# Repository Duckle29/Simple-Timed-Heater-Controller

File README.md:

# Simple-Timed-Heater-Controller
A simple controller used to manage electrical heaters in for example a shed.
This code is compatible with any arduino board. It has however only been tested on my own hardware.

### Libraries used
In order to use the firmware, you will need to have the following libaries in your library folder:

* [LiquidTWI2](https://github.com/lincomatic/LiquidTWI2)
* [Encoder by PJRC](https://www.pjrc.com/teensy/td_libs_Encoder.html)

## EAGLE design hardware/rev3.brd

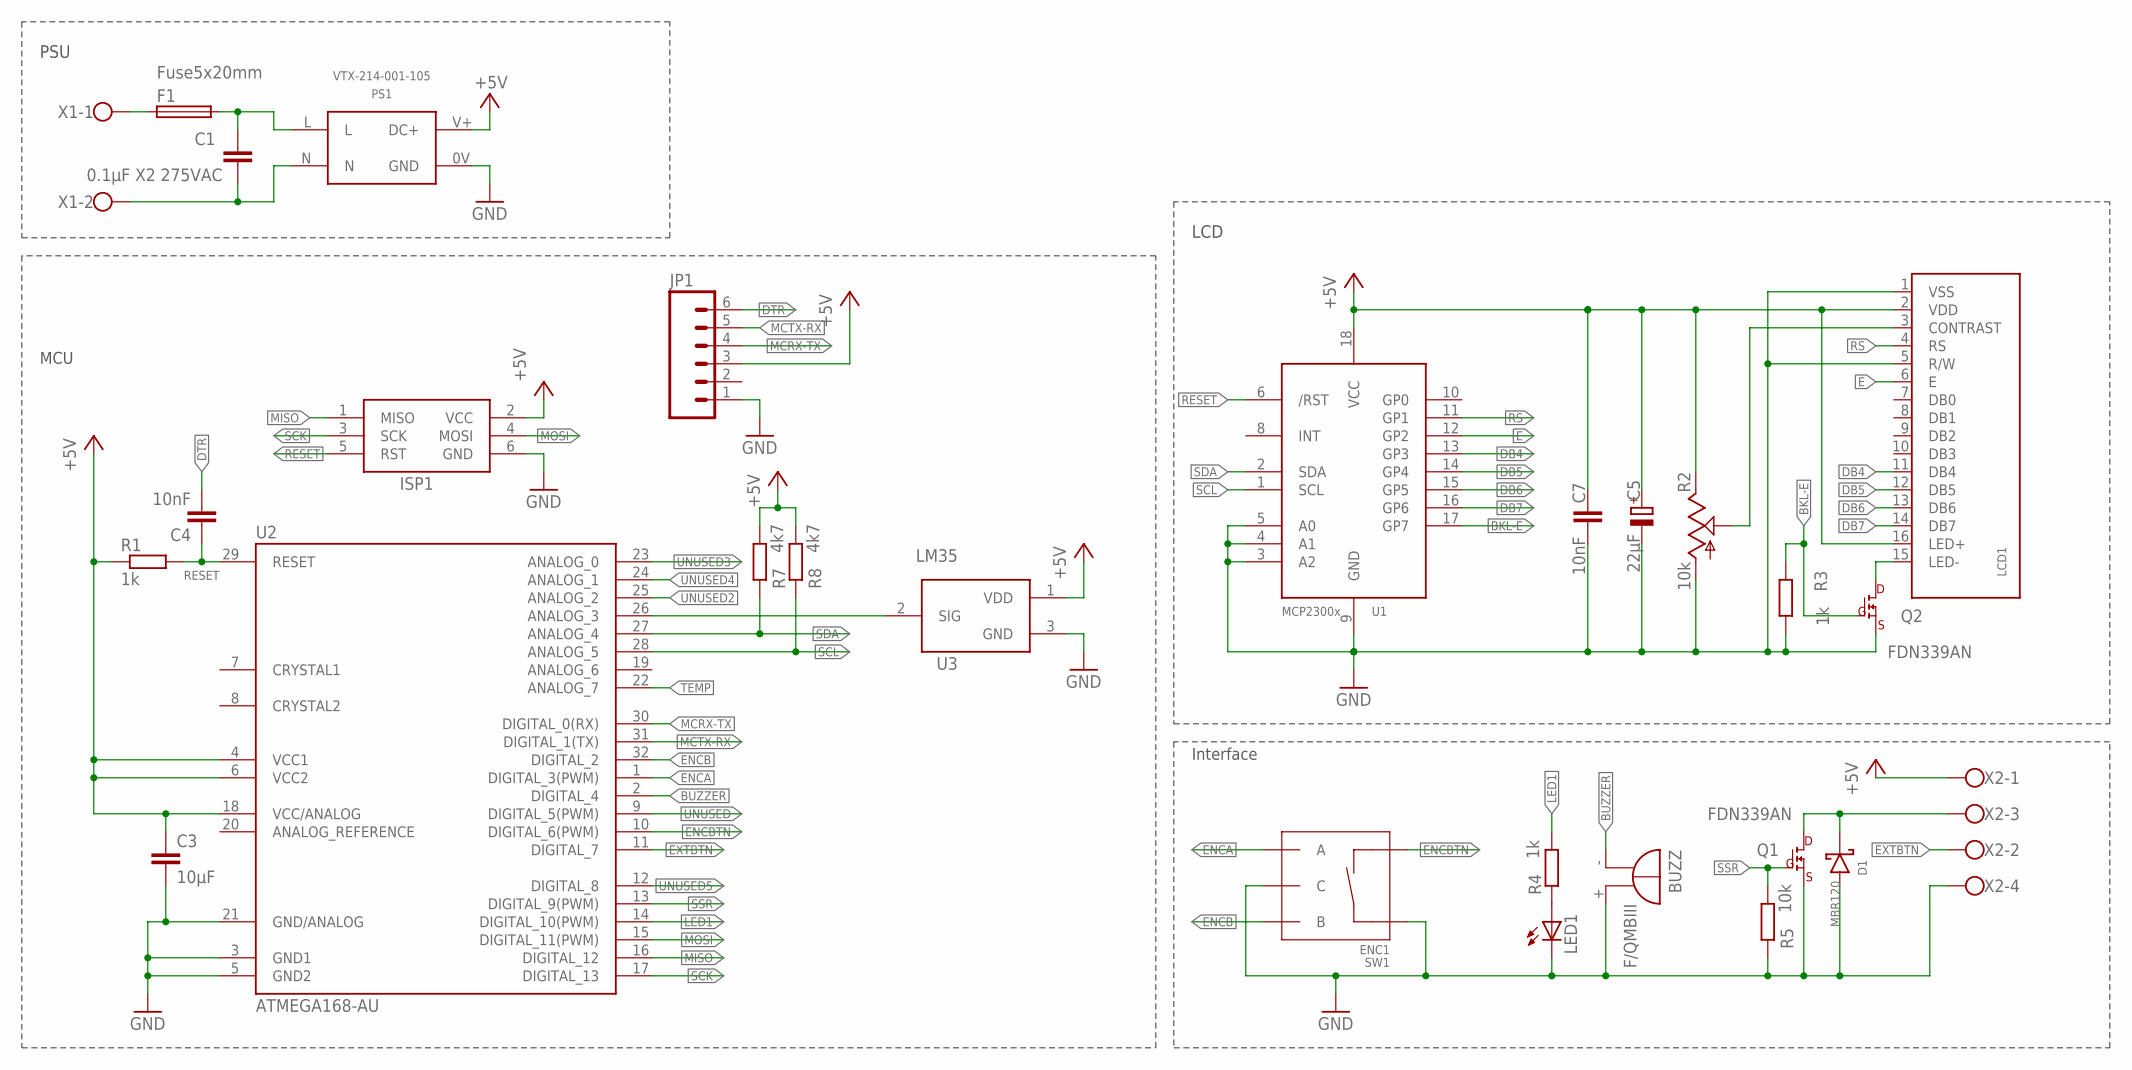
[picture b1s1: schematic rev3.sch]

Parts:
BUZZ: F/QMBIII
C1: 0.1µF X2 275VAC; C102-064X133
C3: 10µF; C3216
C4, C7: 10nF; C1206K
C5: 22µF; E2,5-6E
D1: MBR120; SOD-123FL
F1: Fuse5x20mm; FUSE_HOLDER_5X20MM
ISP1: AVRISP-6; AVRISP
JP1: M06LOCK; 1X06_LOCK
LCD1: HD44780-LCD; 8X2-CHARLCD
LED1: LED5MM
PS1: VTX-214-001-105; VTX-214-001-
Q1, Q2: FDN339AN; SOT23
R1, R3, R4: 1k; R0603
R2: 10k; B64Y
R5: 10k; R0603
R7, R8: 4k7; R0603
SW1: ENC1; ROTARY_ENC_PLAIN
U1: MCP2300X/SO; SO18W
U2: ATMEGA168-AU; TQFP32-08
U3: LM35; TO92-
X1: W237-113
X2: W237-4

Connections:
+5V: C3.1, C5.+, C7.1, ISP1.2 (VCC), JP1.3, LCD1.2 (VDD), LCD1.16 (LED+), PS1.V+ (DC+), R1.1, R2.E, R7.2, R8.2, U1.18 (VCC), U2.4 (VCC1), U2.6 (VCC2), U2.18 (VCC/ANALOG), U3.1 (VDD), X2.1
BKL-E: Q2.1 (GATE), R3.1, U1.17 (GP7)
BUZZER: BUZZ.- (+), U2.2 (DIGITAL_4)
DB4: LCD1.11 (DB4), U1.13 (GP3)
DB5: LCD1.12 (DB5), U1.14 (GP4)
DB6: LCD1.13 (DB6), U1.15 (GP5)
DB7: LCD1.14 (DB7), U1.16 (GP6)
DTR: C4.2, JP1.6
E: LCD1.6 (E), U1.12 (GP2)
ENCA: SW1.A, U2.1 (DIGITAL_3(PWM))
ENCB: SW1.B, U2.32 (DIGITAL_2)
ENCBTN: SW1.SW-, U2.10 (DIGITAL_6(PWM))
EXTBTN: U2.11 (DIGITAL_7), X2.2
GND: BUZZ.+ (-), C3.2, C5.-, C7.2, D1.A, ISP1.6 (GND), JP1.1, LCD1.1 (VSS), LCD1.5 (R/W), LED1.K (C), PS1.0V (GND), Q1.2 (SOURCE), Q2.2 (SOURCE), R2.A, R3.2, R5.1, SW1.C, SW1.SW+, U1.3 (A2), U1.4 (A1), U1.5 (A0), U1.9 (GND), U2.3 (GND1), U2.5 (GND2), U2.21 (GND/ANALOG), U3.3 (GND), X2.4
LED1: R4.2, U2.14 (DIGITAL_10(PWM))
MCRX-TX: JP1.4, U2.30 (DIGITAL_0(RX))
MCTX-RX: JP1.5, U2.31 (DIGITAL_1(TX))
MISO: ISP1.1 (MISO), U2.16 (DIGITAL_12)
MOSI: ISP1.4 (MOSI), U2.15 (DIGITAL_11(PWM))
unnamed: LCD1.3 (CONTRAST), R2.S
unnamed: F1.1, X1.1
unnamed: C1.1, F1.2, PS1.L
unnamed: LCD1.15 (LED-), Q2.3 (DRAIN)
unnamed: U2.26 (ANALOG_3), U3.2 (SIG)
unnamed: LED1.A, R4.1
unnamed: C1.2, PS1.N, X1.2
unnamed: D1.C, Q1.3 (DRAIN), X2.3
RESET: C4.1, ISP1.5 (RST), R1.2, U1.6 (/RST), U2.29 (RESET)
RS: LCD1.4 (RS), U1.11 (GP1)
SCK: ISP1.3 (SCK), U2.17 (DIGITAL_13)
SCL: R8.1, U1.1 (SCL), U2.28 (ANALOG_5)
SDA: R7.1, U1.2 (SDA), U2.27 (ANALOG_4)
SSR: Q1.1 (GATE), R5.2, U2.13 (DIGITAL_9(PWM))
TEMP: U2.22 (ANALOG_7)
UNUSED: U2.9 (DIGITAL_5(PWM))
UNUSED2: U2.25 (ANALOG_2)
UNUSED3: U2.23 (ANALOG_0)
UNUSED4: U2.24 (ANALOG_1)
UNUSED5: U2.12 (DIGITAL_8)

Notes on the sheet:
LCD
MCU
Interface
PSU

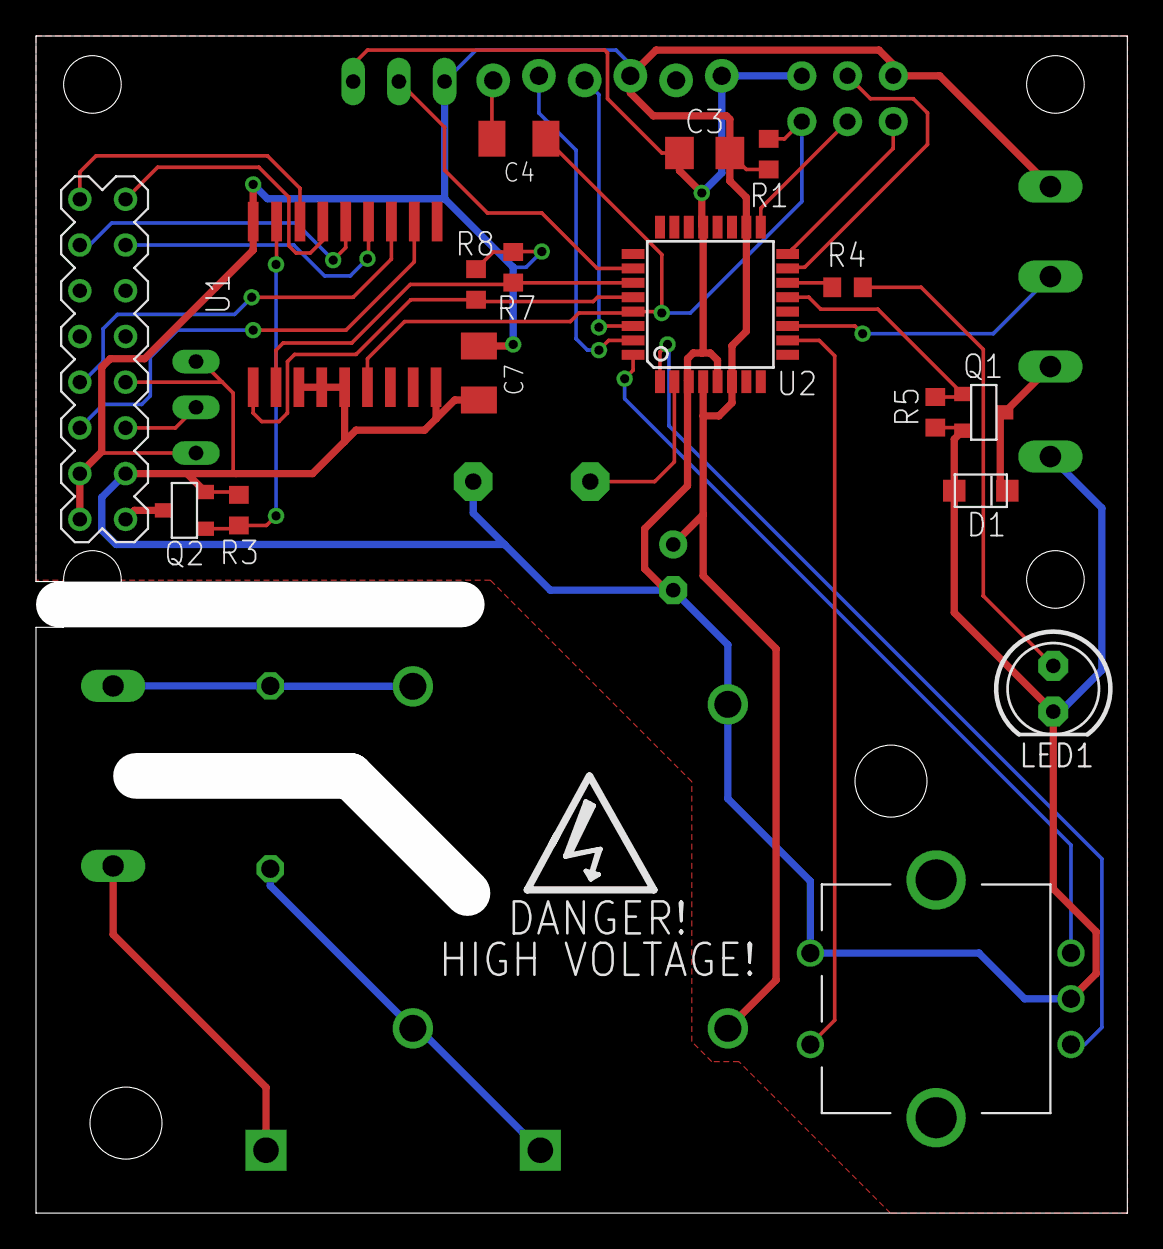
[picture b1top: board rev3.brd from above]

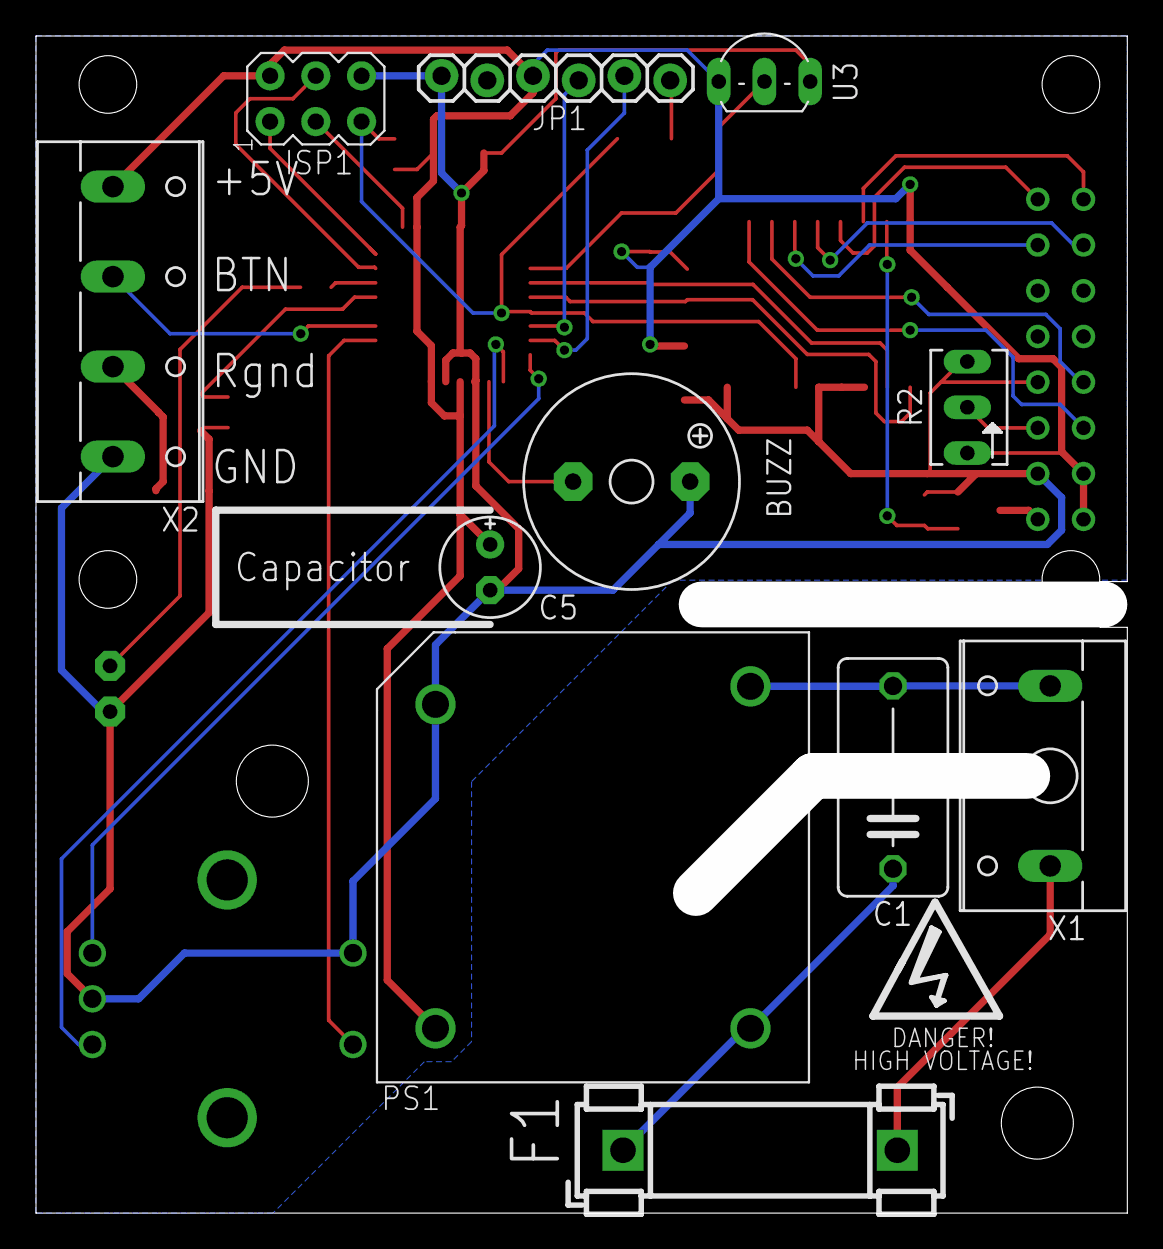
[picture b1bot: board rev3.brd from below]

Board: 2 copper layers, 58.1 x 62.9 mm, 28 parts (11 on the bottom side), 33 nets.

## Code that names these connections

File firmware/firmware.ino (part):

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
// Store the different pins in variables
int tempSens = A3;
int extBtn = 7;
int encBtn = 6;
int SSR = 9;
int redLed = 10;
int buzzer = 4;

// Integers used in the program
int backLightDelay = 15*1000;
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int pressDurationLong = 1000; // Time in milliseconds to press the button for it to be read as a long press
int bounceTime = 10; // Time to wait for a button to debounce in milliseconds

int standbyWarning = 5; // How many minutes before entering standby, should the buzzer start beeping? 0 = off.
int buzzInterval = 3000; // Time between buzzes in ms when the heater is about to enter standby mode

int encVal = 0;
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
  // Set up the inputs and outputs
  pinMode(tempSens, INPUT);
  pinMode(encBtn, INPUT);
  pinMode(extBtn, INPUT);
  pinMode(buzzer, OUTPUT);
  pinMode(SSR, OUTPUT);
  pinMode(redLed, OUTPUT);

  digitalWrite(buzzer, LOW);
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
void buzzControl()
{
  if(millis() - buzzStart < buzzMs) // If the buzz is not yet over, write the buzzer pin high
  {
    digitalWrite(buzzer, HIGH);
  }
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
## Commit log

2015-04-03 Added hardware files
2015-04-03 Moved firmware to seperate folder, and renamed files
2015-04-03 Updated readme to list required libraries
2015-04-23 Added a temperature stabilisation test

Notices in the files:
firmware/firmware.ino:
TODO: License it under LGPL
parts and their libraries:
SparkFun-Electromechanical: Licensing: CC v3.0 Share-Alike You are welcome to use this library for commercial purposes.
